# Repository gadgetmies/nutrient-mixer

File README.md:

# Arduino Hydroponics Nutrient Mixer

Implemented for ESP32 Devkit (v1?) / TTGO T-Display. Requires v2.x of the ESP32 board package.

Send `?` over serial (115200 baud) to list the commands.

## WiFi

There are no network credentials in the code. When no network has been configured, the device starts a hotspot
named `Mix-XXXX` and shows a setup screen with a QR code for joining it. Scan the code with a phone camera (or
join the hotspot with the name and password shown next to the code), choose the network on the setup page that
opens and enter its password. If the page does not open by itself, go to http://192.168.4.1. The credentials
are stored in the ESP32's flash.

The hotspot password is generated on first boot. Any key returns from the setup screen to the menu; the screen
can be shown again from WiFi > Show QR code (or `w qr`).

With a configured network the device keeps reconnecting in the background instead of opening the hotspot.
To change the network, use WiFi > Forget WiFi in the menu or send `w reset`. Requires the WiFiManager library
(tzapu, 2.0 or newer).

## Sensors

The pH and TDS sensors are powered through the shift register, one at a time so that the probes do not
interfere with each other. A sensor is read only after it has been powered for 2 seconds
(`sensorWarmUpMilliseconds`).

## Sensor calibration

The pH and TDS sensors use a two point calibration that is stored in flash. To calibrate, put the probe in the
reference solution, wait until the readings are stable (e.g. `l 60`) and send:

- `k ph 4.0` and `k ph 7.0` with pH 4.0 and 7.0 buffers
- `k tds 707` with a TDS standard solution (a value below 100 ppm, e.g. `k tds 0` in distilled water, sets the low point)

`k` shows the current calibration and `k reset` restores the defaults.

## Float switches

A triggered float switch blocks its pump immediately and lights the error LED. The pump continues once the
switch has stayed released for a second.

## Menu

The menu follows `menu.txt` on the `local-main` branch. Pump amounts (dose run time, also used per adjustment
round), reservoir pump times and the targets are saved in flash. Requires GEM 1.5 or newer (`GEMSpinner`).

## Simulator

`simulator/` runs this firmware on a Mac against a simulated T-Display, the mixer board (`eagle/`) and the
pumps, reservoirs and sensors around it, with a browser UI: `cd simulator && make run`. See
[simulator/README.md](simulator/README.md).

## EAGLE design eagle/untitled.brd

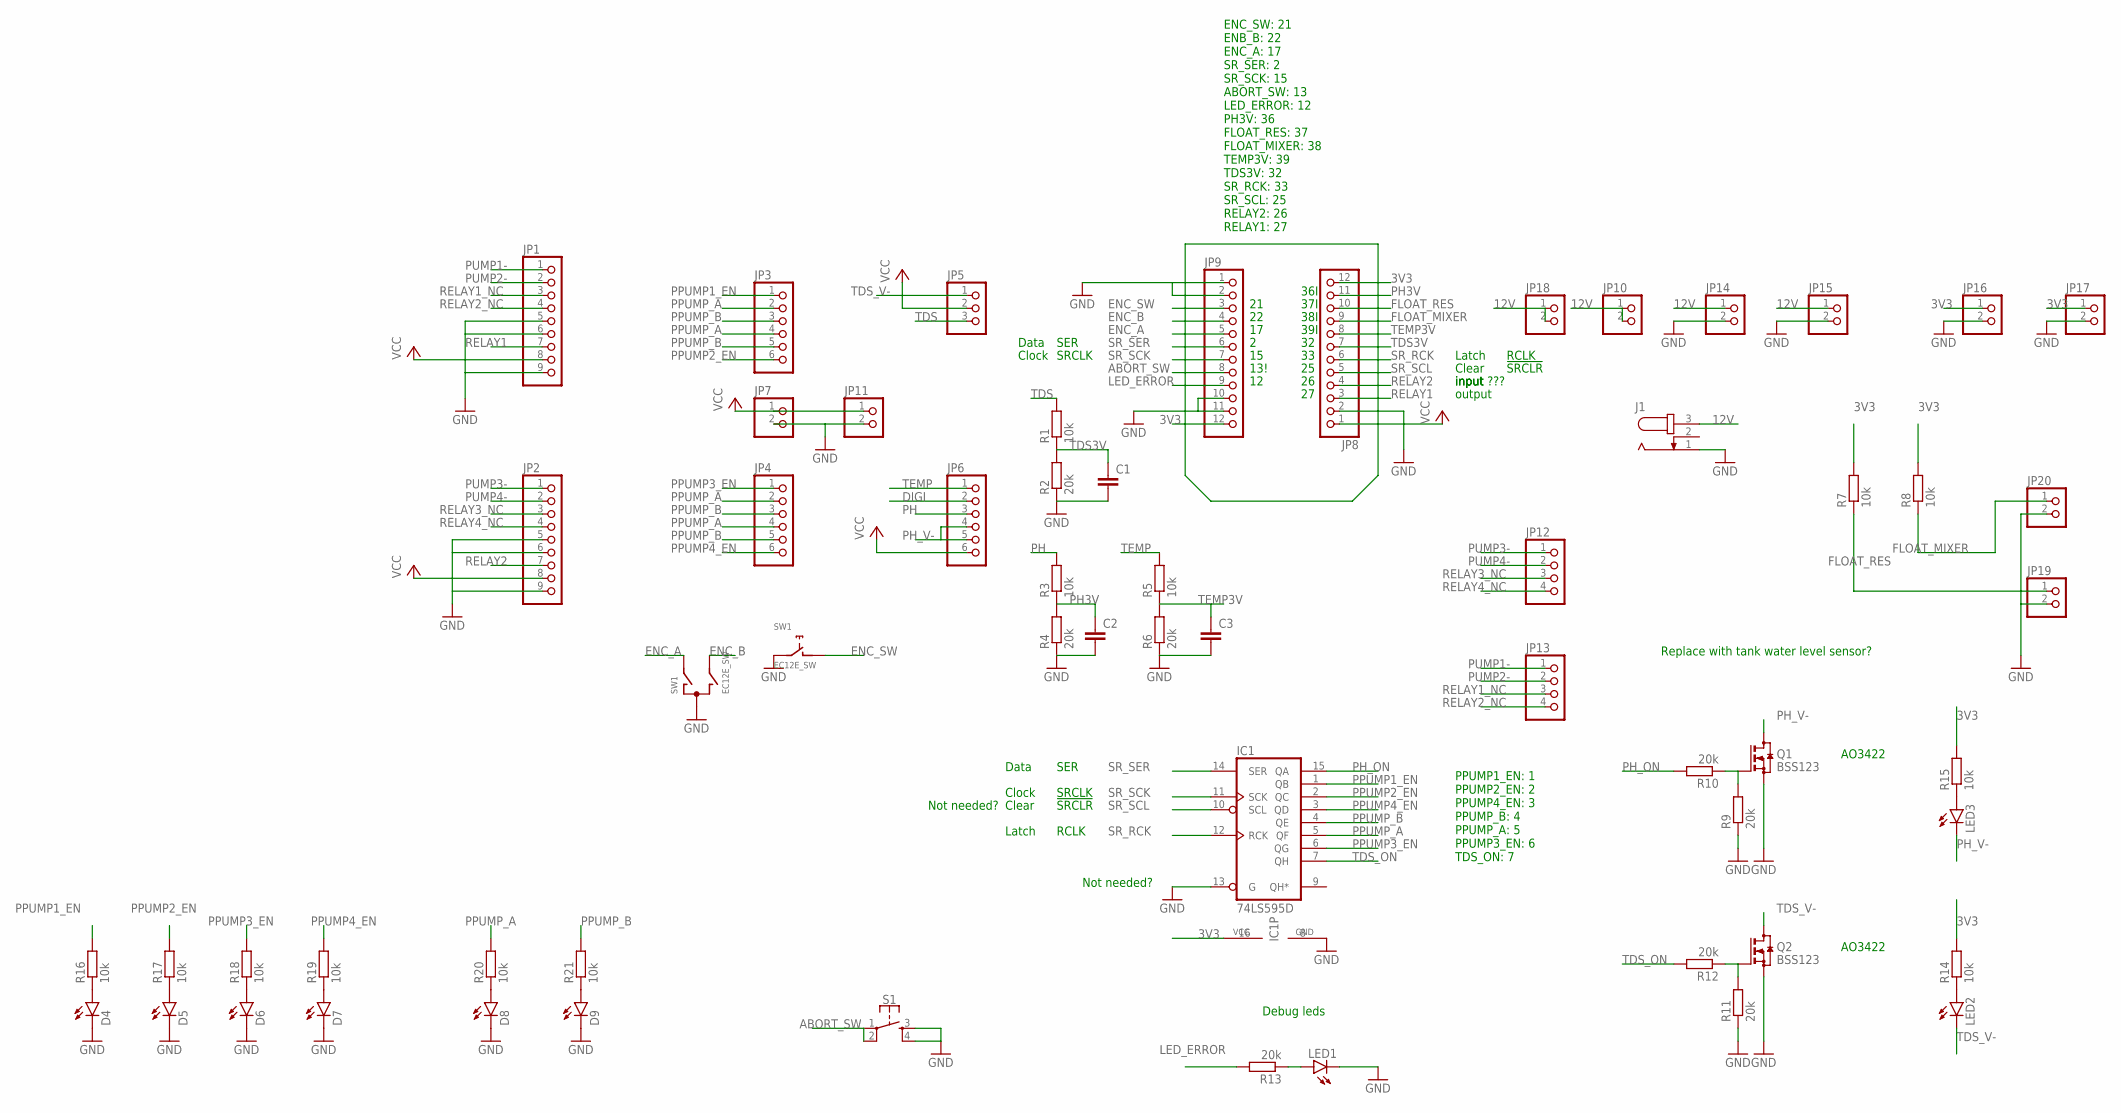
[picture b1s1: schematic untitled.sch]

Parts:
C1, C2, C3: C-EUC0805; C0805
D4, D5, D6, D7, D8, D9: LEDCHIP-LED0603; CHIP-LED0603
IC1: 74LS595D; SO16
J1: JACK-PLUG1; SPC4078
JP1, JP2: PINHD-1X9; 1X09
JP3, JP4, JP6: PINHD-1X6; 1X06
JP5: PINHD-1X3; 1X03
JP7, JP10, JP11, JP14, JP15, JP16, JP17, JP18, JP19, JP20: PINHD-1X2; 1X02
JP8, JP9: PINHD-1X12; 1X12
JP12, JP13: PINHD-1X4; 1X04
LED1, LED2, LED3: LEDCHIP-LED0603; CHIP-LED0603
Q1, Q2: BSS123; SOT23
R1, R3, R5, R7, R8, R14, R15, R16, R17, R18, R19, R20, R21: 10k; R0805
R2, R4, R6, R9, R10, R11, R12, R13: 20k; R0805
S1: MOMENTARY-SWITCH-SPST-2-SMD-5.2MM; TACTILE_SWITCH_SMD_5.2MM
SW1: EC12E_SW; ALPS_EC12E_SW

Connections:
3V3: IC1.16 (VCC), JP8.12, JP9.12, JP16.1, JP17.1, R7.2, R8.2, R14.2, R15.2
12V: J1.3, JP10.1, JP10.2, JP14.1, JP15.1, JP18.1, JP18.2
ABORT_SW: JP9.8, S1.1, S1.2
DIGI: JP6.2
ENC_A: JP9.5, SW1.A
ENC_B: JP9.4, SW1.B
ENC_SW: JP9.3, SW1.D (1)
FLOAT_MIXER: JP8.9, JP20.1, R8.1
FLOAT_RES: JP8.10, JP19.1, R7.1
GND: C1.2, C2.2, C3.2, D4.C, D5.C, D6.C, D7.C, D8.C, D9.C, IC1.8 (GND), IC1.13 (G), J1.1, JP1.5, JP1.6, JP1.9, JP2.5, JP2.6, JP2.9, JP7.2, JP8.2, JP9.1, JP9.2, JP9.10, JP9.11, JP11.2, JP14.2, JP15.2, JP16.2, JP17.2, JP19.2, JP20.2, LED1.C, Q1.2 (S), Q2.2 (S), R2.1, R4.1, R6.1, R9.1, R11.1, S1.3, S1.4, SW1.C, SW1.E (2)
LED_ERROR: JP9.9, R13.2
unnamed: LED2.A, R14.1
unnamed: LED1.A, R13.1
unnamed: LED3.A, R15.1
unnamed: D4.A, R16.1
unnamed: D5.A, R17.1
unnamed: D6.A, R18.1
unnamed: D7.A, R19.1
unnamed: D8.A, R20.1
unnamed: D9.A, R21.1
unnamed: Q1.1 (G), R9.2, R10.1
unnamed: Q2.1 (G), R11.2, R12.1
PH: JP6.3, R3.2
PH3V: C2.1, JP8.11, R3.1, R4.2
PH_ON: IC1.15 (QA), R10.2
PH_V-: JP6.4, JP6.5, LED3.C, Q1.3 (D)
PPUMP1_EN: IC1.1 (QB), JP3.1, R16.2
PPUMP2_EN: IC1.2 (QC), JP3.6, R17.2
PPUMP3_EN: IC1.6 (QG), JP4.1, R18.2
PPUMP4_EN: IC1.3 (QD), JP4.6, R19.2
PPUMP_A: IC1.5 (QF), JP3.2, JP3.4, JP4.2, JP4.4, R20.2
PPUMP_B: IC1.4 (QE), JP3.3, JP3.5, JP4.3, JP4.5, R21.2
PUMP1-: JP1.1, JP13.1
PUMP2-: JP1.2, JP13.2
PUMP3-: JP2.1, JP12.1
PUMP4-: JP2.2, JP12.2
RELAY1: JP1.7, JP8.3
RELAY1_NC: JP1.3, JP13.3
RELAY2: JP2.7, JP8.4
RELAY2_NC: JP1.4, JP13.4
RELAY3_NC: JP2.3, JP12.3
RELAY4_NC: JP2.4, JP12.4
SR_RCK: IC1.12 (RCK), JP8.6
SR_SCK: IC1.11 (SCK), JP9.7
SR_SCL: IC1.10 (SCL), JP8.5
SR_SER: IC1.14 (SER), JP9.6
TDS: JP5.3, R1.2
TDS3V: C1.1, JP8.7, R1.1, R2.2
TDS_ON: IC1.7 (QH), R12.2
TDS_V-: JP5.1, LED2.C, Q2.3 (D)
TEMP: JP6.1, R5.2
TEMP3V: C3.1, JP8.8, R5.1, R6.2
VCC: JP1.8, JP2.8, JP5.2, JP6.6, JP7.1, JP8.1, JP11.1

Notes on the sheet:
Replace with tank water level sensor?
39I
38I
37I
36I
13!
input
input ???
output
Not needed?
AO3422
Debug leds
ENC_SW: 21 ENB_B: 22 ENC_A: 17 SR_SER: 2 SR_SCK: 15 ABORT_SW: 13 LED_ERROR: 12 PH3V: 36 FLOAT_RES: 37 FLOAT_MIXER: 38 TEMP3V: 39 TDS3V: 32 SR_RCK: 33 SR_SCL: 25 RELAY2: 26 RELAY1: 27
PPUMP1_EN: 1 PPUMP2_EN: 2 PPUMP4_EN: 3 PPUMP_B: 4 PPUMP_A: 5 PPUMP3_EN: 6 TDS_ON: 7
SER
SRCLK
!SRCLR
RCLK
Data
Clock
Clear
Latch

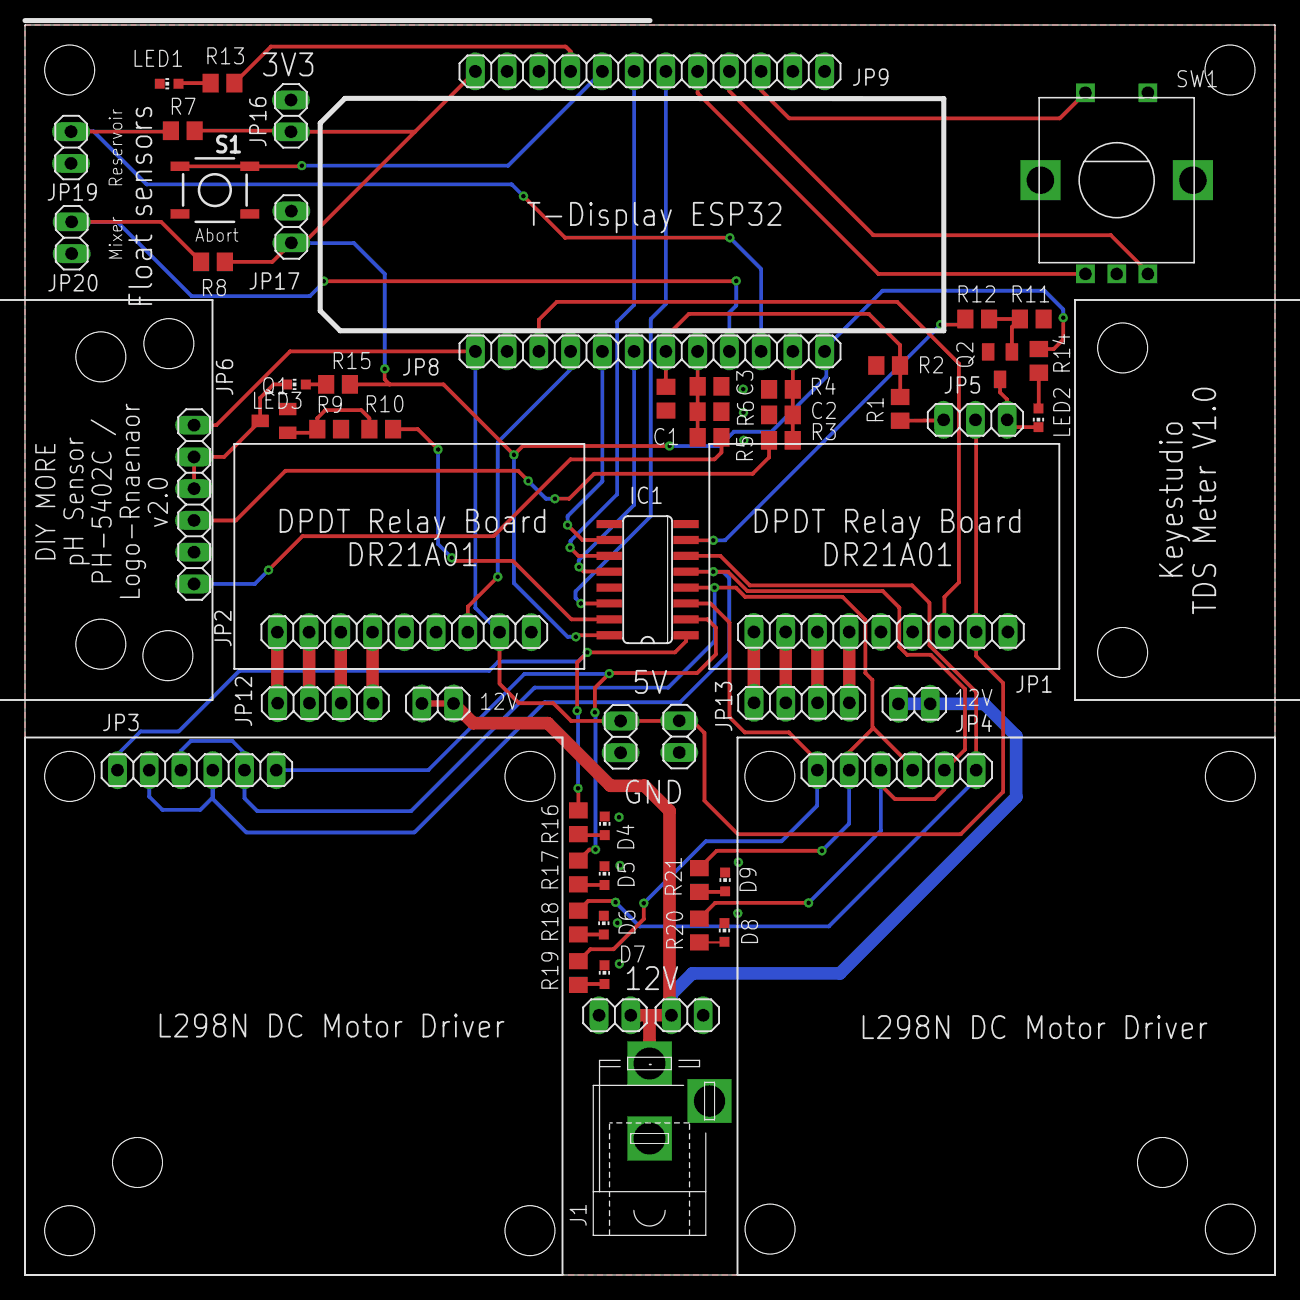
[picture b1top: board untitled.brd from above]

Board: 2 copper layers, 100.0 x 100.0 mm, 59 parts (0 on the bottom side), 52 nets.

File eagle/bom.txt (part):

Partlist exported from /Users/mkiiski/Documents/EAGLE/projects/nutrient mixer/untitled.sch at 15.9.2025 14.59

Part Value    Device                            Package                  Description                                         MF MPN          OC_FARNELL OC_NEWARK POPULARITY PROD_ID    SF_SKU    SPICEPREFIX
C1            C-EUC0805                         C0805                    CAPACITOR, European symbol                                                               88                              C          
C2            C-EUC0805                         C0805                    CAPACITOR, European symbol                                                               88                              C          
C3            C-EUC0805                         C0805                    CAPACITOR, European symbol                                                               88                              C          
D4            LEDCHIP-LED0603                   CHIP-LED0603             LED                                                                                      26                                         
D5            LEDCHIP-LED0603                   CHIP-LED0603             LED                                                                                      26                                         
D6            LEDCHIP-LED0603                   CHIP-LED0603             LED                                                                                      26                                         
D7            LEDCHIP-LED0603                   CHIP-LED0603             LED                                                                                      26                                         
D8            LEDCHIP-LED0603                   CHIP-LED0603             LED                                                                                      26                                         
D9            LEDCHIP-LED0603                   CHIP-LED0603             LED                                                                                      26                                         
IC1  74LS595D 74LS595D                          SO16                     8-bit SHIFT REGISTER, output latch                                                       0                                          
J1            JACK-PLUG1                        SPC4078                  DC POWER JACK                                                       unknown    unknown   3                                          
JP1           PINHD-1X9                         1X09                     PIN HEADER                                                                               13                                         
JP2           PINHD-1X9                         1X09                     PIN HEADER                                                                               13                                         
JP3           PINHD-1X6                         1X06                     PIN HEADER                                                                               79                                         
JP4           PINHD-1X6                         1X06                     PIN HEADER                                                                               79                                         
JP5           PINHD-1X3                         1X03                     PIN HEADER                                                                               92                                         
JP6           PINHD-1X6                         1X06                     PIN HEADER                                                                               79                                         
JP7           PINHD-1X2                         1X02                     PIN HEADER                                                                               98                                         
JP8           PINHD-1X12                        1X12                     PIN HEADER                                                                               28                                         
JP9           PINHD-1X12                        1X12                     PIN HEADER                                                                               28                                         
JP10          PINHD-1X2                         1X02                     PIN HEADER                                                                               98                                         
JP11          PINHD-1X2                         1X02                     PIN HEADER                                                                               98                                         
JP12          PINHD-1X4                         1X04                     PIN HEADER                                                                               91                                         
JP13          PINHD-1X4                         1X04                     PIN HEADER                                                                               91                                         
JP14          PINHD-1X2                         1X02                     PIN HEADER                                                                               98                                         
JP15          PINHD-1X2                         1X02                     PIN HEADER                                                                               98                                         
JP16          PINHD-1X2                         1X02                     PIN HEADER                                                                               98                                         
JP17          PINHD-1X2                         1X02                     PIN HEADER                                                                               98                                         
JP18          PINHD-1X2                         1X02                     PIN HEADER                                                                               98                                         
JP19          PINHD-1X2                         1X02                     PIN HEADER                                                                               98                                         
JP20          PINHD-1X2                         1X02                     PIN HEADER                                                                               98                                         
LED1          LEDCHIP-LED0603                   CHIP-LED0603             LED                                                                                      26                                         
LED2          LEDCHIP-LED0603                   CHIP-LED0603             LED                                                                                      26                                         
LED3          LEDCHIP-LED0603                   CHIP-LED0603             LED                                                                                      26                                         
Q1   BSS123   BSS123                            SOT23                    N-CHANNEL MOS FET                                                                        21                                         
Q2   BSS123   BSS123                            SOT23                    N-CHANNEL MOS FET                                                                        21                                         
R1   10k      R-EU_R0805                        R0805                    RESISTOR, European symbol                                                                86                              R          
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
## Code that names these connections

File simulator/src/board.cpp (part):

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      return buttons[IO0] ? LOW : HIGH;
    case pins::BUTTON_IO35:  // External pull-up on the T-Display
      return buttons[IO35] ? LOW : HIGH;
    case pins::ENC_SW:
      if (buttons[ENCODER_BUTTON]) return LOW;
      break;
    case pins::ABORT_SW:
      if (buttons[ABORT_BUTTON]) return LOW;
      break;
    case pins::ENC_A:
      if (encoderA) return LOW;
      break;
    case pins::ENC_B:
      if (encoderB) return LOW;
      break;
    case pins::FLOAT_RES:  // R7 pull-up, the float switch shorts to GND
      return world.plant.floatClosed ? LOW : HIGH;
    case pins::FLOAT_MIXER:  // R8 pull-up
      return world.mixer.floatClosed ? LOW : HIGH;
  }
  // GPIO 34-39 have no internal pull resistors
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  const int level = resolveLevel(pin);
  if (level == p.level) return;
  p.level = level;
  if (pin == pins::SR_SER || pin == pins::SR_SCK || pin == pins::SR_RCK || pin == pins::SR_SCL) {
    shiftRegisterPinChanged(pin, level);
  }
  if (p.isr) {
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// 74HC595: data shifts in on the rising edge of SRCLK, the outputs latch on the rising edge of RCLK and a low
// !SRCLR clears the shift register (not the outputs)
void Board::shiftRegisterPinChanged(uint8_t pin, int level) {
  const bool clear = pinState[pins::SR_SCL].level == LOW;
  if (pin == pins::SR_SCL && clear) srShift = 0;
  if (pin == pins::SR_SCK) {
    if (level && !srClockLevel && !clear) {
      srShift = (uint8_t)((srShift << 1) | (pinState[pins::SR_SER].level ? 1 : 0));
    }
    srClockLevel = level;
  }
  if (pin == pins::SR_RCK) {
    if (level && !srLatchLevel) {
      srLatch = srShift;
      const bool phOn = srOutput(sr::PH_ON);
      const bool tdsOn = srOutput(sr::TDS_ON);
      if (phOn && !phBoard.powered) phBoard.poweredAt = now;
      if (tdsOn && !tdsBoard.powered) tdsBoard.poweredAt = now;
      phBoard.powered = phOn;
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  const bool sameLiquid = world.phProbe.wet && world.tdsProbe.wet && world.phProbe.location <= 1
                          && world.phProbe.location == world.tdsProbe.location;

  if (pin == pins::PH3V || pin == pins::TEMP3V) {
    if (!phBoard.powered) return fabs(noise(1));
    const double warmUp = 1 - exp(-(now - phBoard.poweredAt) / sensorWarmUpSeconds);
    double output;
    if (pin == pins::TEMP3V) {
      output = 1700 + 12 * temperature;  // Thermistor output of the PH-4502C (not calibrated)
    } else if (params.choice("fault.phProbe") == 1 || !world.phProbe.wet) {
      // Floating electrode input: the output wanders and picks up hum
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    return output + noise(params.get("noise"));
  }

  if (pin == pins::TDS3V) {
    if (!tdsBoard.powered) return fabs(noise(1));
    const double warmUp = 1 - exp(-(now - tdsBoard.poweredAt) / sensorWarmUpSeconds);
    double output = 0;
    if (params.choice("fault.tdsProbe") == 0 && world.tdsProbe.wet) {
      // Conductivity (and the board output) rises about 2 % per degree
      const double tds = world.tdsProbe.tdsPpm * (1 + 0.02 * (temperature - 25));
      output = (tds - tdsAtZeroMilliVolts) * tdsMilliVoltsPerPpm * (1 + params.get("tds.gain") / 100);
      if (bothPowered && sameLiquid) output += 40 + noise(10);
    }
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      updateInput(pins::BUTTON_IO35);
      break;
    case ENCODER_BUTTON:
      updateInput(pins::ENC_SW);
      break;
    case ABORT_BUTTON:
      updateInput(pins::ABORT_SW);
      break;
    default:
      break;
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void Board::setEncoderContacts(bool aClosed, bool bClosed) {
  encoderA = aClosed;
  encoderB = bClosed;
  updateInput(pins::ENC_A);
  updateInput(pins::ENC_B);
}

void Board::update(double time) {
  now = time;
  updateInput(pins::FLOAT_RES);
  updateInput(pins::FLOAT_MIXER);
}

bool Board::relayEnergized(int relay) const {
  const uint8_t pin = relay == 0 ? pins::RELAY1 : pins::RELAY2;
  const Pin &p = pinState[pin];
  if ((p.mode & OUTPUT) != OUTPUT) return false;  // Undriven input: the relay board's pull resistor keeps it off
  const int activeLevel = params.choice("relay.activeLevel") == 0 ? HIGH : LOW;
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// L298N: ENx enables the H-bridge; INa high / INb low drives forwards, the opposite backwards and equal inputs
// brake the motor. On this board IN1/IN3 are both PPUMP_A and IN2/IN4 are both PPUMP_B.
int Board::l298nOutput(int driver, int channel) const {
  static const int enableBits[2][2] = {{sr::PPUMP1_EN, sr::PPUMP2_EN}, {sr::PPUMP3_EN, sr::PPUMP4_EN}};
  if (!srOutput(enableBits[driver][channel])) return 0;
  const bool a = srOutput(sr::PPUMP_A);
  const bool b = srOutput(sr::PPUMP_B);
  if (a && !b) return 1;
  if (!a && b) return -1;
  return 0;
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  json.set("shiftRegister", srLatch);
  json.set("shiftRegisterInternal", srShift);
  Json leds = Json::object();
  leds.set("LED1", pinState[pins::LED_ERROR].level == HIGH && (pinState[pins::LED_ERROR].mode & OUTPUT) == OUTPUT);
  leds.set("LED2", tdsBoard.powered);
  leds.set("LED3", phBoard.powered);
  leds.set("D4", srOutput(sr::PPUMP1_EN));
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  json.set("relays", relays);
  Json drivers = Json::array();
  for (int driver = 0; driver < 2; ++driver) {
    static const int enableBits[2][2] = {{sr::PPUMP1_EN, sr::PPUMP2_EN}, {sr::PPUMP3_EN, sr::PPUMP4_EN}};
    Json d = Json::object();
    d.set("ena", srOutput(enableBits[driver][0]));
    d.set("enb", srOutput(enableBits[driver][1]));
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
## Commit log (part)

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2024-05-25 Reset after abort
2024-05-25 WIP pH adjustment
2024-05-25 WIP remove CQRobot
2024-05-25 WIP TDS
2024-05-25 WIP Plot
2024-05-25 Pins
2024-05-25 Changing these to the comment values will break the functionality
2024-05-25 Parse adjustment parameters in correct order
2024-05-25 Fix adjust all
2024-05-25 Add logging to measure

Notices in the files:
parts and their libraries:
SparkFun-Switches: Licensing: Creative Commons ShareAlike 4.0 International - https://creativecommons.org/licenses/by-sa/4.0
